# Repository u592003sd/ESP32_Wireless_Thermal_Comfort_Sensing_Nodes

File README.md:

# ESP32 Based Wireless Thermal Confort Sensing Nodes
- Created a ESP32 shield compatible with DS18B20 Temp. Sensor & DHT11 RH Sensor. (Best bang for buck)
- Created a ESP32 shield compatible with HDC1008 Temperature Sensor which has 0.2°C Accuracy.
- Optimized routing to 1 layer PCB to match college fabrication facility guidelines.
- Project Documentation folder can be used to refer to System Design Choices and Thermal Sensing Experimentation

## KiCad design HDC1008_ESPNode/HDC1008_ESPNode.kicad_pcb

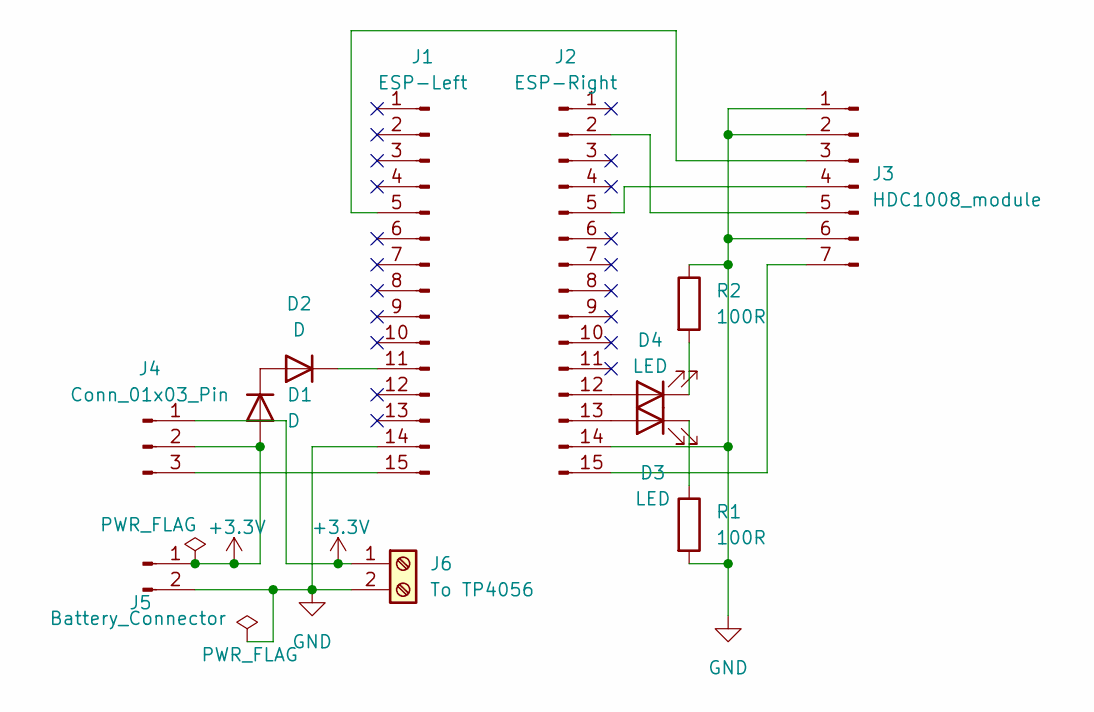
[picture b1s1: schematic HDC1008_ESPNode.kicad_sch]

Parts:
D1, D2: D; D_DO-41_SOD81_P10.16mm_Horizontal
D3, D4: LED; LED_D3.0mm_Clear
J1: ESP-Left; PinHeader_1x15_P2.54mm_Vertical
J2: ESP-Right; PinHeader_1x15_P2.54mm_Vertical
J3: HDC1008_module; PinHeader_1x07_P2.54mm_Vertical
J4: Conn_01x03_Pin; PinHeader_1x03_P2.54mm_Vertical
J5: Battery_Connector; JST_XH_B2B-XH-A_1x02_P2.50mm_Vertical
J6: To TP4056; TerminalBlock_RND_205-00276_1x02_P5.00mm_Vertical
R1, R2: 100R; R_Axial_DIN0207_L6.3mm_D2.5mm_P10.16mm_Horizontal

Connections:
+3.3V: D1.2 (A), J4.1, J4.2, J5.1, J6.1
GND: J1.14, J2.14, J3.1, J3.2, J3.6, J5.2, J6.2, R1.2, R2.1
unnamed: D1.1 (K), D2.2 (A)
unnamed: D2.1 (K), J1.11
unnamed: D3.2 (A), J2.13
unnamed: D3.1 (K), R1.1
unnamed: D4.2 (A), J2.12
unnamed: D4.1 (K), R2.2
unnamed: J1.5, J3.3
unnamed: J1.15, J4.3
unnamed: J2.2, J3.5
unnamed: J2.5, J3.4
unnamed: J2.15, J3.7

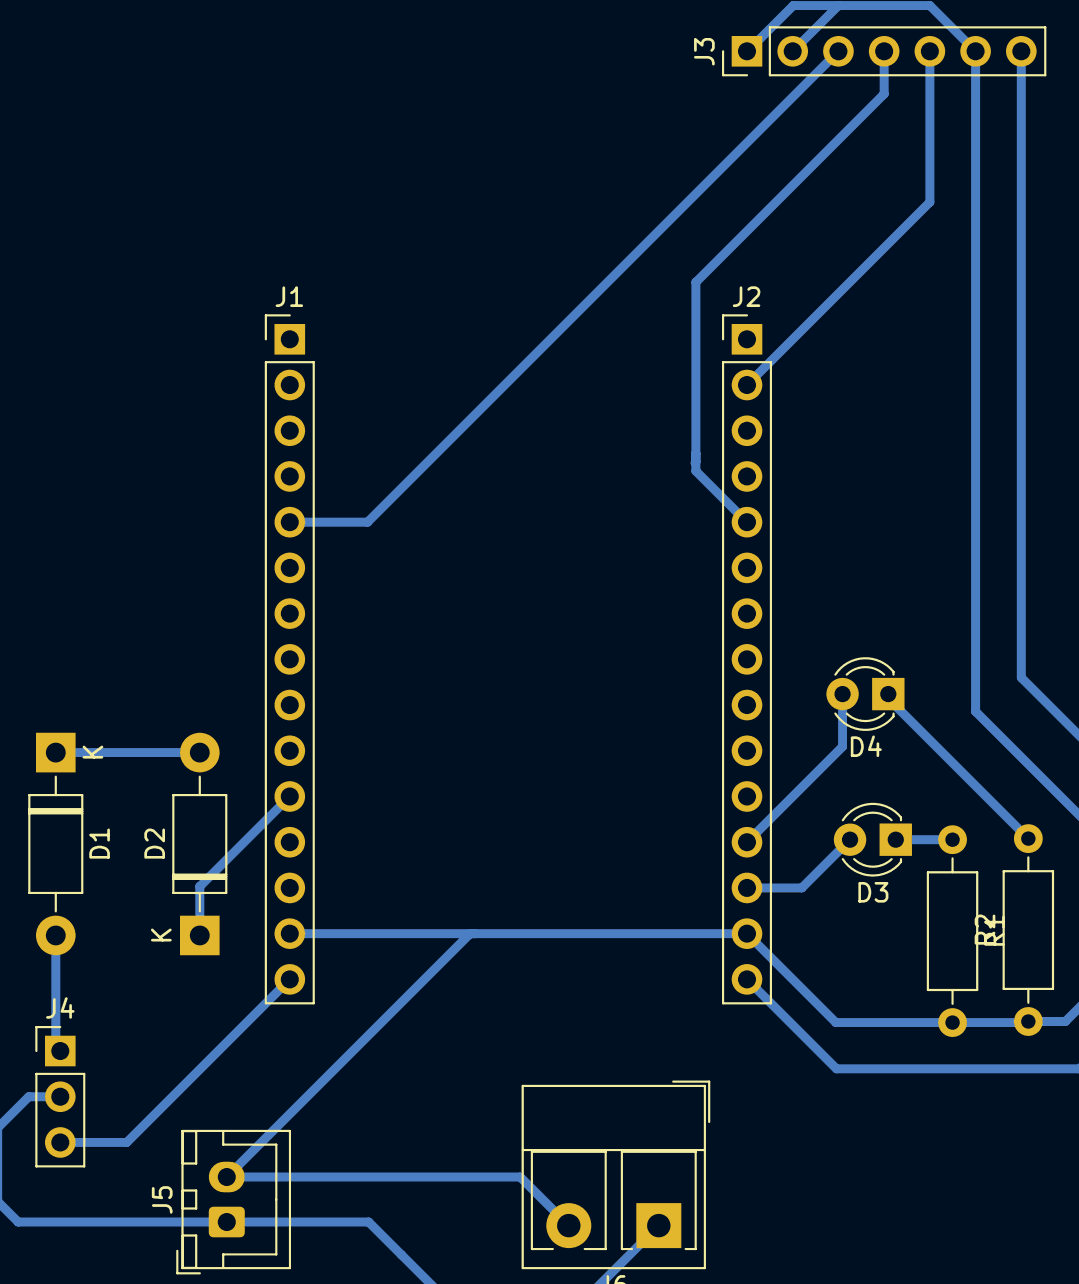
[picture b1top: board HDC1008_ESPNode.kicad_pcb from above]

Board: 2 copper layers, 12 parts (0 on the bottom side), 13 nets.

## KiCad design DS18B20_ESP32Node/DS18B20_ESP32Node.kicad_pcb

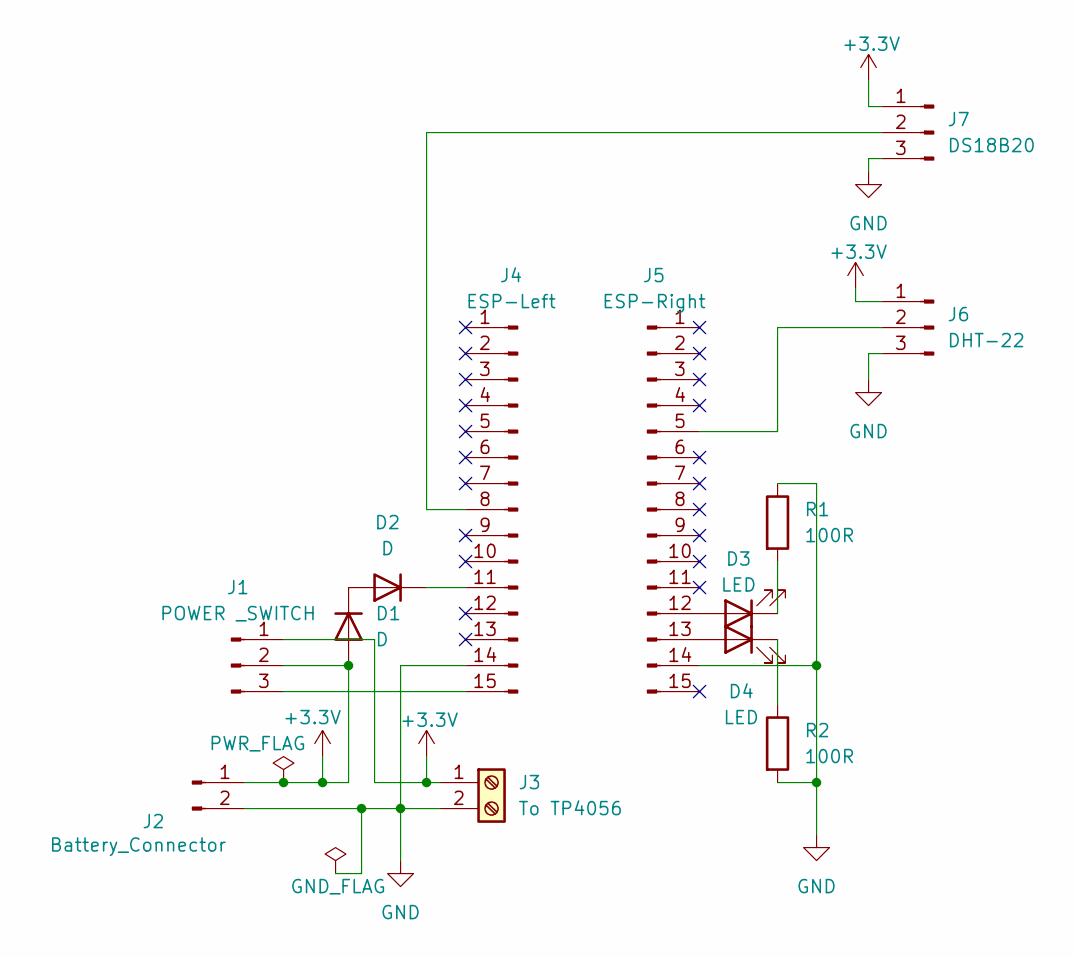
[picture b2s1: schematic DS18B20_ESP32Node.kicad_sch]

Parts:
D1, D2: D; D_DO-41_SOD81_P10.16mm_Horizontal
D3, D4: LED; LED_D5.0mm
J1: POWER _SWITCH; PinHeader_1x03_P2.54mm_Vertical
J2: Battery_Connector; JST_XH_B2B-XH-A_1x02_P2.50mm_Vertical
J3: To TP4056; TerminalBlock_RND_205-00232_1x02_P5.08mm_Horizontal
J4: ESP-Left; PinHeader_1x15_P2.54mm_Vertical
J5: ESP-Right; PinHeader_1x15_P2.54mm_Vertical
J6: DHT-22; PinHeader_1x03_P2.54mm_Vertical
J7: DS18B20; PinHeader_1x03_P2.54mm_Vertical
R1, R2: 100R; R_Axial_DIN0207_L6.3mm_D2.5mm_P10.16mm_Horizontal

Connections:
+3.3V: D1.2 (A), J1.1, J1.2, J2.1, J3.1, J6.1, J7.1
GND: J2.2, J3.2, J4.14, J5.14, J6.3, J7.3, R1.1, R2.2
unnamed: D1.1 (K), D2.2 (A)
unnamed: D2.1 (K), J4.11
unnamed: D3.2 (A), J5.12
unnamed: D3.1 (K), R1.2
unnamed: D4.2 (A), J5.13
unnamed: D4.1 (K), R2.1
unnamed: J1.3, J4.15
unnamed: J4.8, J7.2
unnamed: J5.5, J6.2

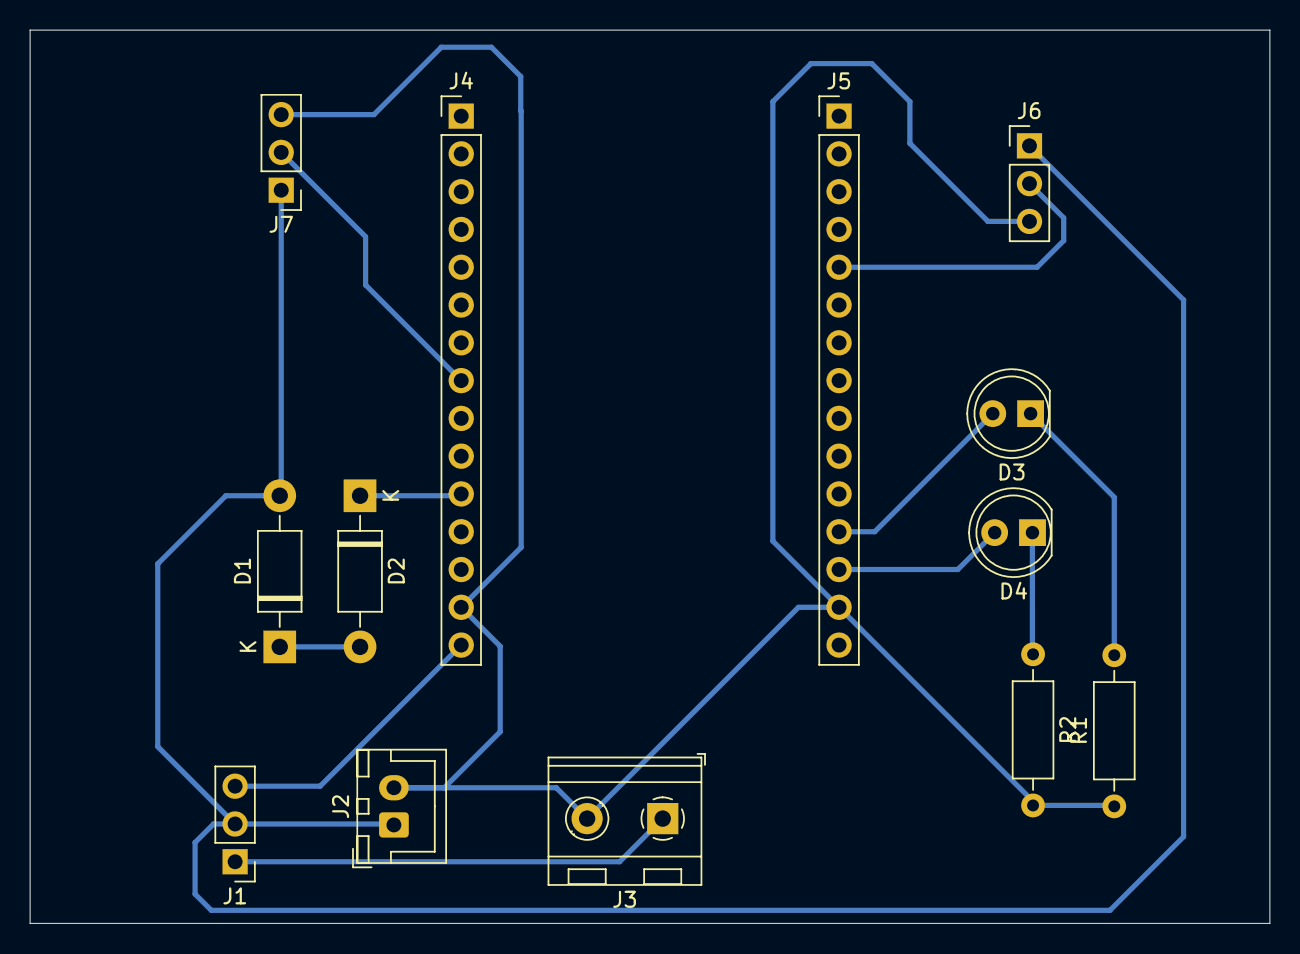
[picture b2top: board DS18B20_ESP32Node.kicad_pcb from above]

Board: 2 copper layers, 83.3 x 60.1 mm, 13 parts (0 on the bottom side), 11 nets.

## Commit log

2026-04-15 Add PCB designs used for Thermal Comfort Sensing
    - Add DS18B20 based low cost design
    - Add HDC1008 based design with greater thermal sense accuracy
    - Add Schematics for power measurement node
2026-04-15 Add Porject Documentation - Add Project Documentation folder to conatin all project documentation - Add ESP32 Wireless Sensor Node system Documentation - Add Project Report containing Experiment and 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
2026-04-15 Create README.md
    - Add Description to navigate repository.
